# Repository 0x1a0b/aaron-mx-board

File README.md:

Forked from https://git.okoyono.de/aaron/mx-board

mxboard
=======

Cherry MX breakout board for Arduino, RaspberryPi and other boards.

Order here: https://oshpark.com/shared_projects/PogDjaIS

Arduino Sample
==============

```arduino
const int buttonPin = 10;
const int ledPin = 11;

void setup() {
  pinMode(buttonPin, INPUT);
  pinMode(ledPin, OUTPUT);
}

void loop() {
  // The switches are equiped with pull-down resistors. So if the
  // button is pressed, you read a HIGH, if the button is released
  // you read a LOW.
  digitalWrite(ledPin, digitalRead(buttonPin));
}
```

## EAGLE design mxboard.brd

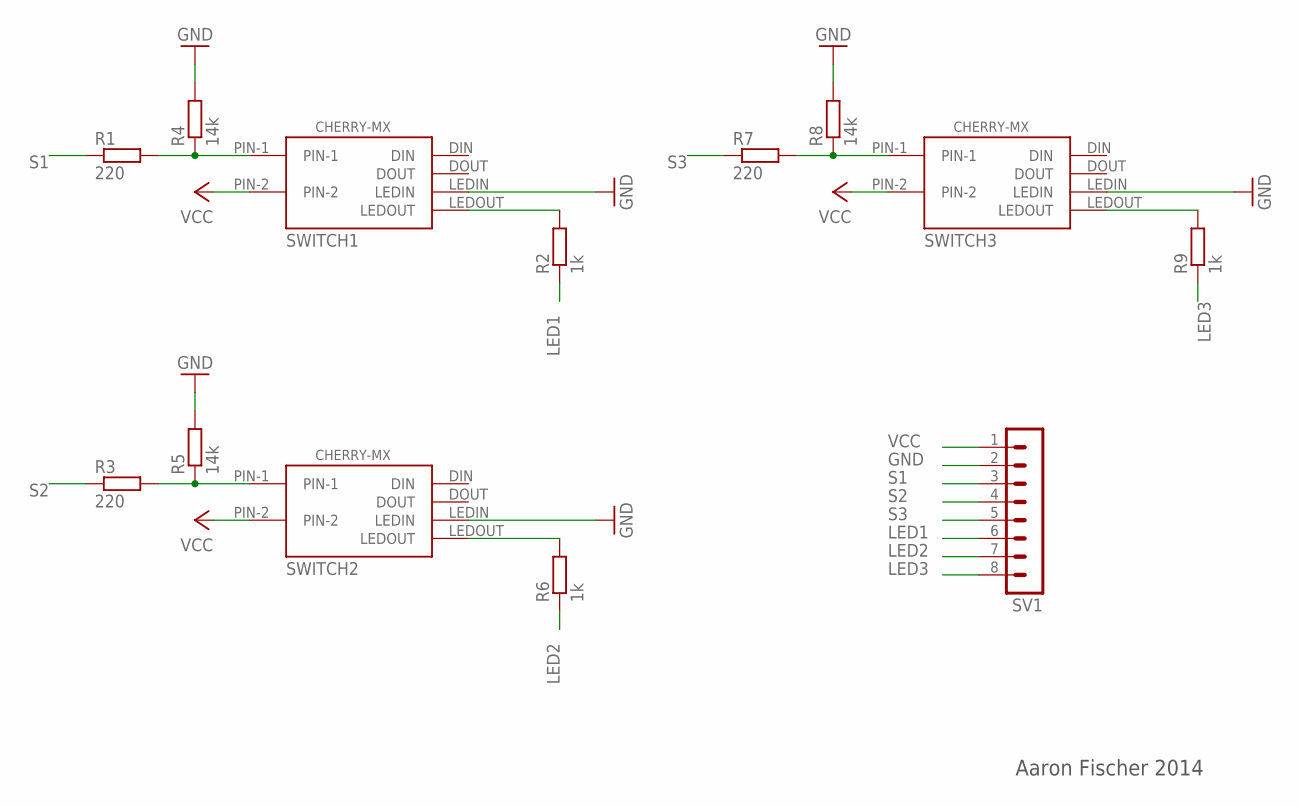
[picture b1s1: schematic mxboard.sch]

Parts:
R1, R3, R7: 220; R0805
R2, R6, R9: 1k; R0805
R4, R5, R8: 14k; R0805
SV1: MA08-1
SWITCH1, SWITCH2, SWITCH3: CHERRY-MX-I

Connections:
GND: R4.2, R5.2, R8.2, SV1.2, SWITCH1.LEDIN, SWITCH2.LEDIN, SWITCH3.LEDIN
LED1: R2.1, SV1.6
LED2: R6.1, SV1.7
LED3: R9.1, SV1.8
unnamed: R1.2, R4.1, SWITCH1.PIN-1
unnamed: R2.2, SWITCH1.LEDOUT
unnamed: R3.2, R5.1, SWITCH2.PIN-1
unnamed: R6.2, SWITCH2.LEDOUT
unnamed: R7.2, R8.1, SWITCH3.PIN-1
unnamed: R9.2, SWITCH3.LEDOUT
S1: R1.1, SV1.3
S2: R3.1, SV1.4
S3: R7.1, SV1.5
VCC: SV1.1, SWITCH1.PIN-2, SWITCH2.PIN-2, SWITCH3.PIN-2

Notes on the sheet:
Aaron Fischer 2014

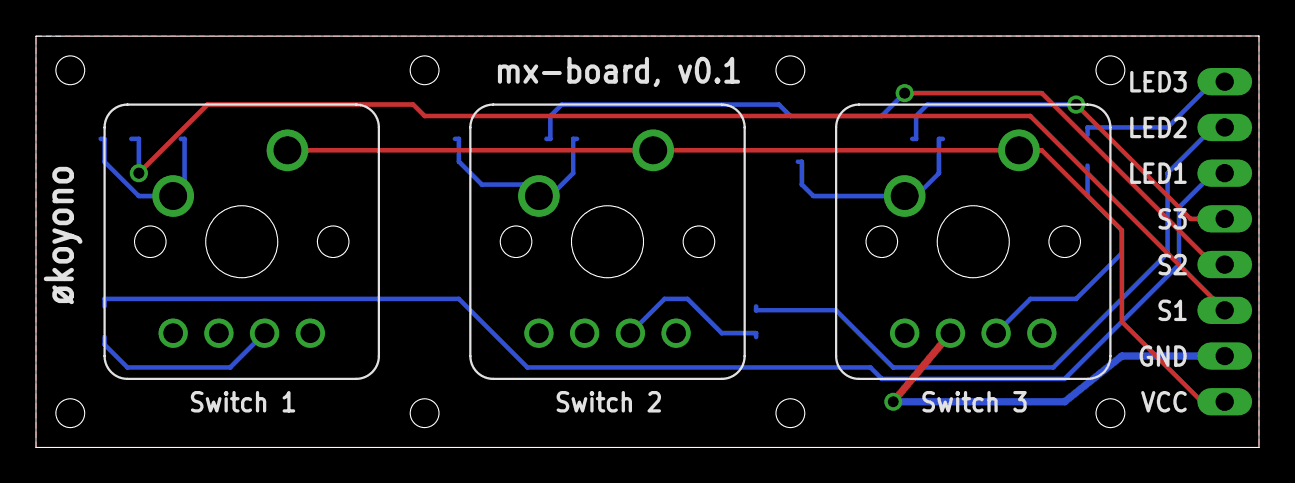
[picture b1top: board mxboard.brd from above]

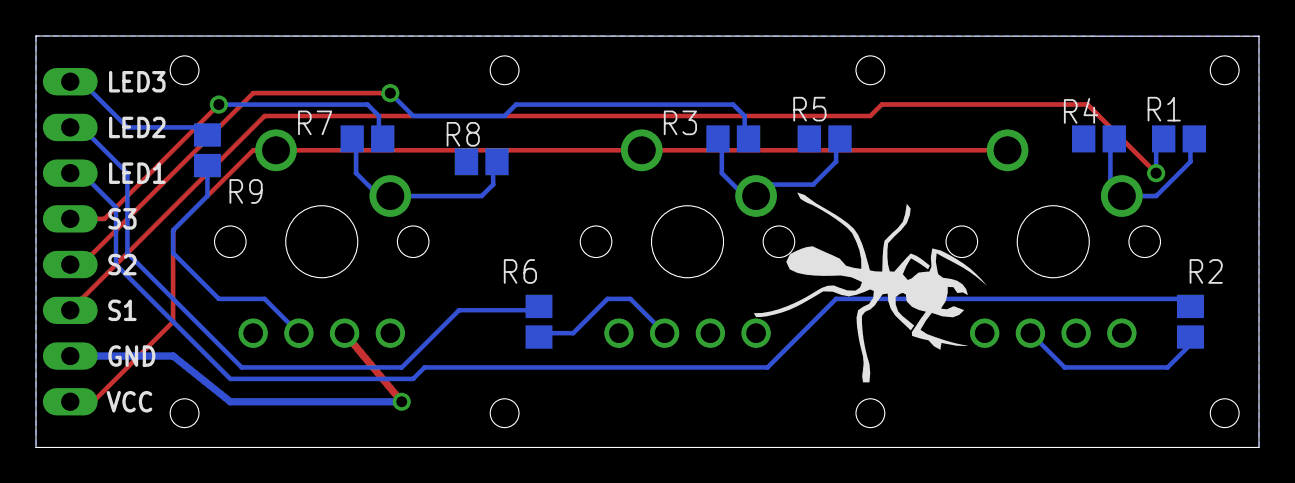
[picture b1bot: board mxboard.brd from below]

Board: 2 copper layers, 67.9 x 22.9 mm, 13 parts (9 on the bottom side), 14 nets.

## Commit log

2014-12-24 Add the pcb and schematics.
2014-12-24 Add images
2014-12-24 Add code sample.
2020-07-02 import note
